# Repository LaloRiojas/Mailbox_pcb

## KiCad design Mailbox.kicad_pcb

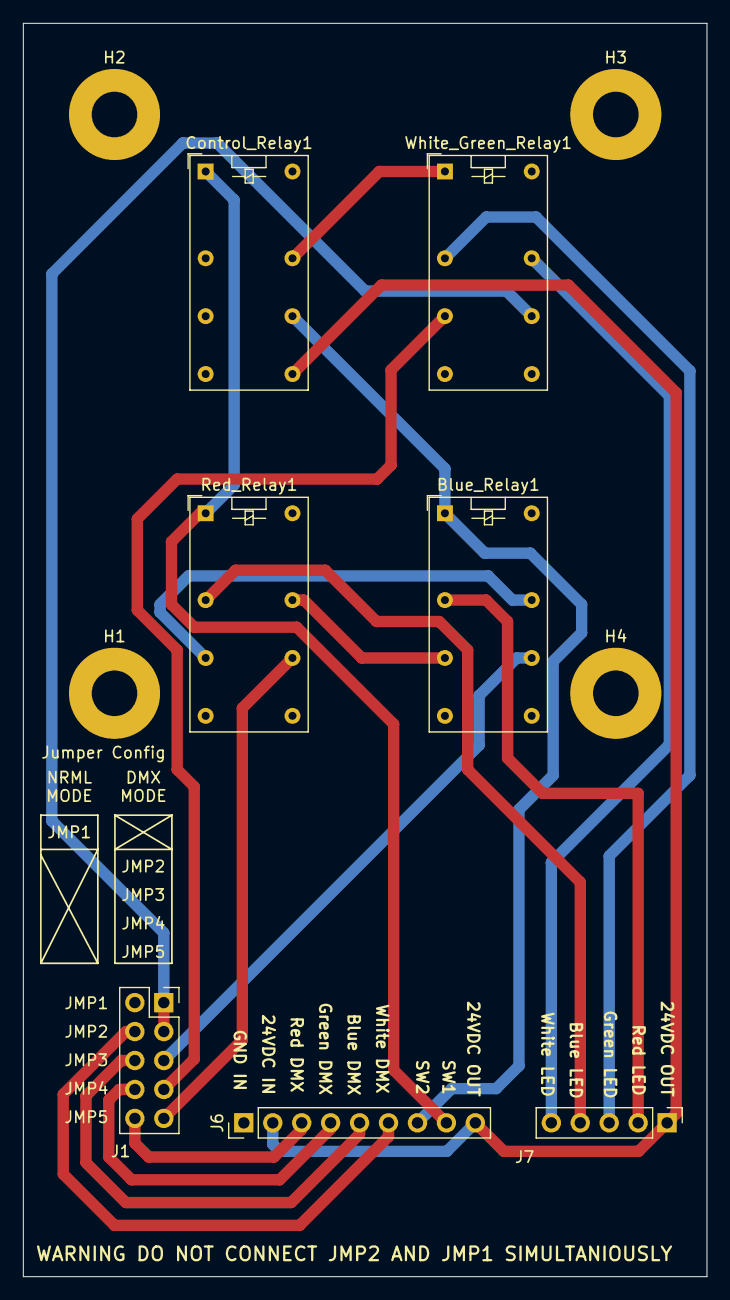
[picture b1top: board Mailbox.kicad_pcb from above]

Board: 2 copper layers, 60.0 x 110.0 mm, 11 parts (0 on the bottom side), 19 nets.

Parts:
Blue_Relay1: G5V-2; Relay_DPDT_Omron_G5V-2
Control_Relay1: G5V-2; Relay_DPDT_Omron_G5V-2
H1, H2, H3, H4: MountingHole_Pad; MountingHole_4mm_Pad
J1: Jumpers; PinSocket_2x05_P2.54mm_Vertical
J6: DMXINPUTS; PinHeader_1x09_P2.54mm_Vertical
J7: LEDOUTPUTS; PinHeader_1x05_P2.54mm_Vertical
Red_Relay1: G5V-2; Relay_DPDT_Omron_G5V-2
White_Green_Relay1: G5V-2; Relay_DPDT_Omron_G5V-2

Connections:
+24V: Control_Relay1.9, J6.2, J6.9, J7.1
BlueDMX: J1.3a, J6.5
BlueLED: J7.4, Red_Relay1.4
BlueSource: Blue_Relay1.11, J1.3b
BlueSwitch: Blue_Relay1.1, Control_Relay1.11, J6.7
GND: Blue_Relay1.9, Blue_Relay1.16, Control_Relay1.16, H1.1, H2.1, H3.1, H4.1, J1.1a, J6.1, Red_Relay1.9, Red_Relay1.16, White_Green_Relay1.16
GreenDMX: J1.4a, J6.4
GreenLED: J7.3, White_Green_Relay1.4
GreenSource: J1.4b, White_Green_Relay1.6
unnamed: Blue_Relay1.6, Red_Relay1.13
unnamed: Blue_Relay1.13, Red_Relay1.6
unnamed: Control_Relay1.13, White_Green_Relay1.1
RedDMX: J1.5a, J6.3
RedLED: Blue_Relay1.4, J7.2
RedSource: J1.5b, Red_Relay1.11
RedSwitch: Control_Relay1.1, J6.8, Red_Relay1.1
WhiteDMX: J1.2a, J6.6
WhiteLED: J7.5, White_Green_Relay1.13
WhiteSource: J1.1b, J1.2b, White_Green_Relay1.11

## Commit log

2024-11-09 decided on esp32-mini because of ethernet feature.
2024-11-09 addeed a ground plane and fixed some track routeing.
